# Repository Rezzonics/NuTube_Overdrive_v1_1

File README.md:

# NuTube_Overdrive_v1_1 (EAGLE 6.3.0)
NuTube Overdrive guitar pedal

Eagle CAD 6.3.0:
- Eagle CAD Schematics (.sch)
- Eagle CAD Layout (.brd)
- Bill of Materials (txt, csv, xlsx)
- Components library (.lbr)

FreeCAD 16.0:
 - 3D CAD NuTube Overdrive enclosure
 
A <a href="https://www.youtube.com/watch?v=pDtBdqI9vC8&list=PLVcOAdxtwYCBdqzgB6T4JSNhljZ__4p3t">guitar pedal test video Youtube playlist<a>

# Disclaimer:
This is just an amateur pedal with no intention for profit or to infringe any trademark.
Tube Screamer is a trademark of Hoshino Gakki Co.
This pedal is not for sale. If you want to buy a similar pedal I recommend you <a href="http://www.ibanez.com/products/u_effect_page18.php?year=2018&amp;area_id=&amp;cat_id=6&amp;series_id=153&amp;effect_id=39">Ibanez NTS Screamer<a>

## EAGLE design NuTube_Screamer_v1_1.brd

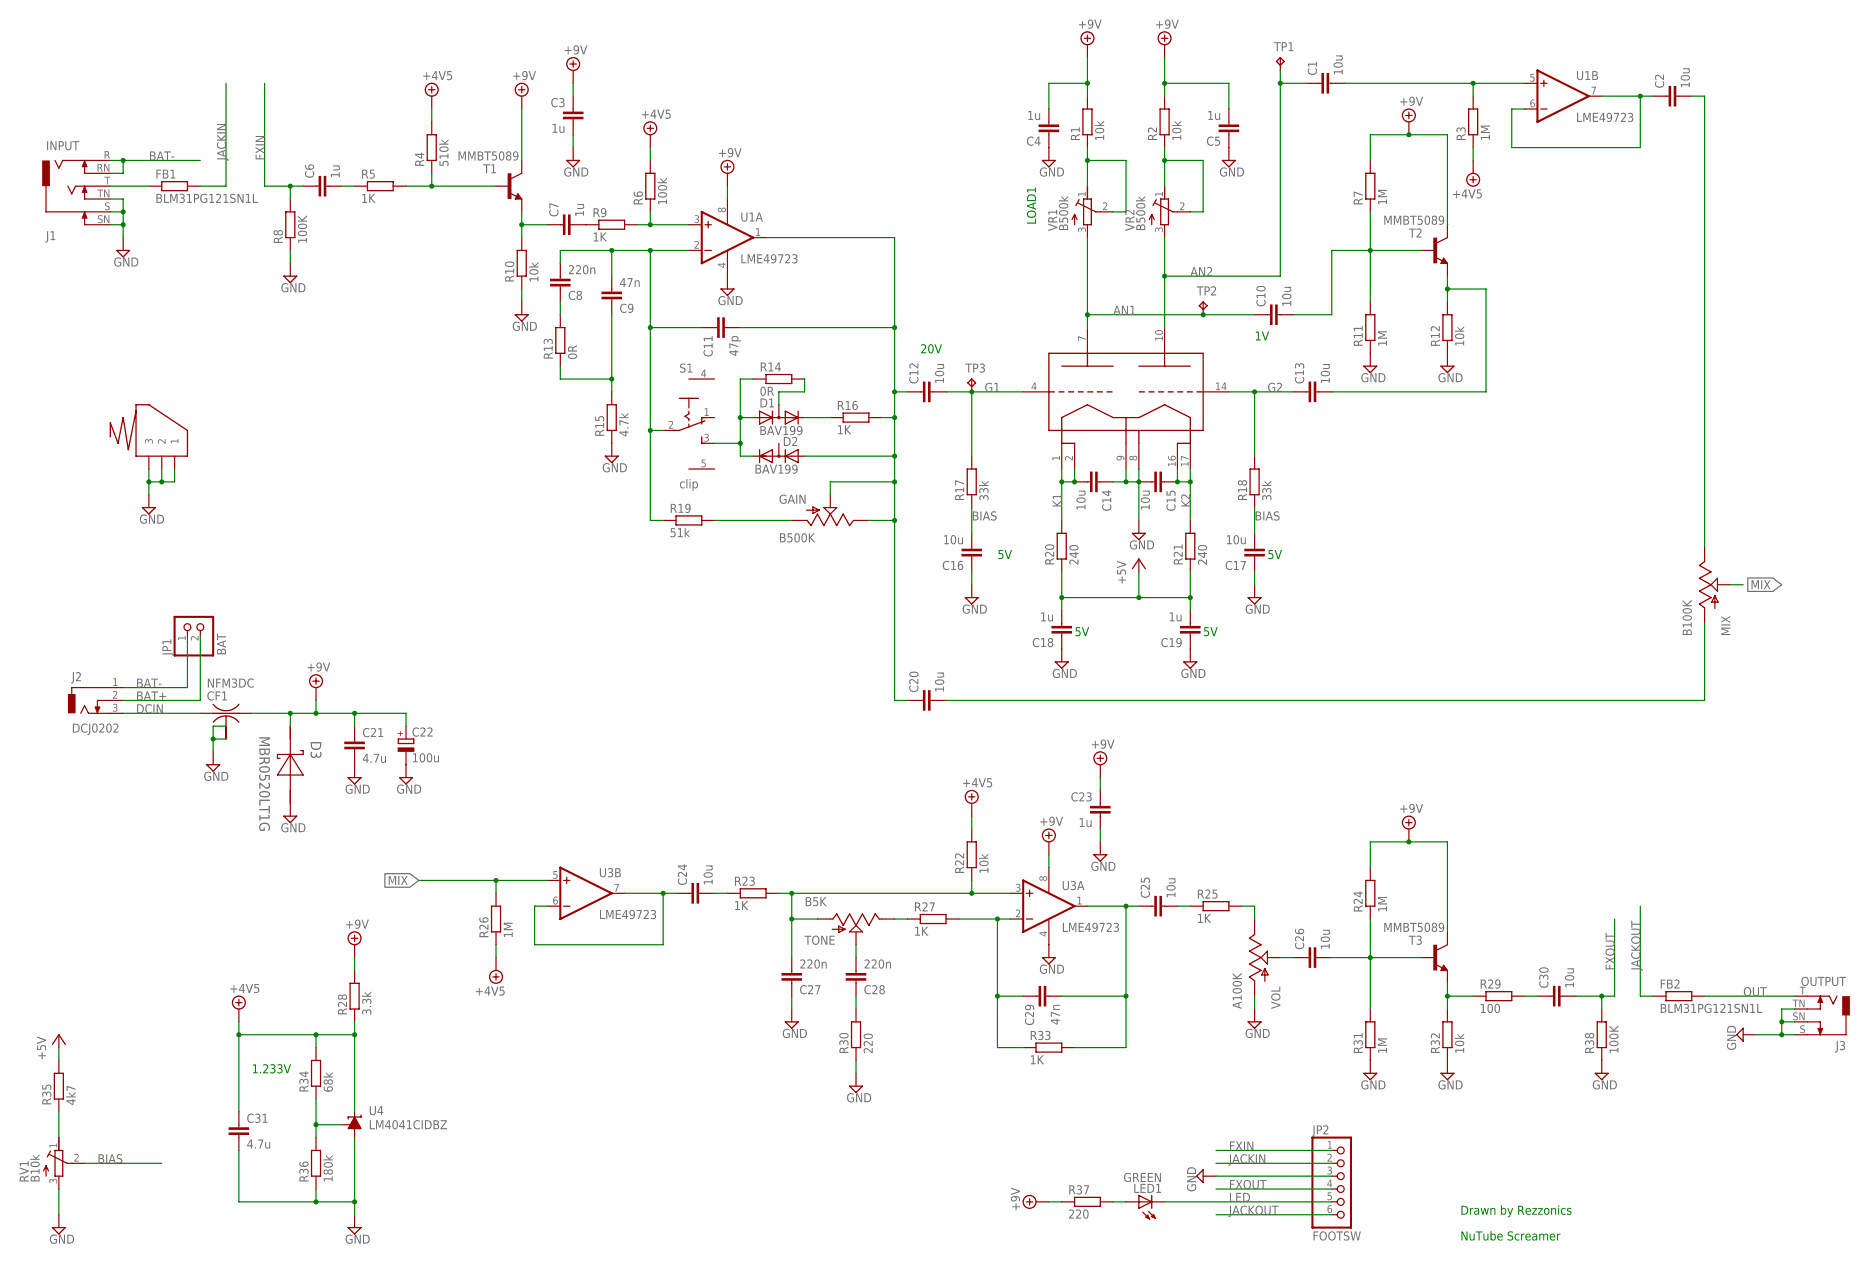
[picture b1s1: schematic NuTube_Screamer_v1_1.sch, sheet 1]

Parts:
C1, C2, C10, C12, C14, C15, C16, C17, C20, C24, C25, C26, C30: 10u; C0805K; MPN GRM21BR6YA106KE43L
C3, C6, C7, C23: 1u; C0603K; MPN GRM188R71H104KA93D
C4, C5, C18, C19: 1u; C0603K; MPN C1608X5R1H105K080AB
C8, C27, C28: 220n; C0603K; MPN GRM188R71H104KA93D
C9, C29: 47n; C0603K; MPN GRM188R71H104KA93D
C11: 47p; C0603K; MPN GRM188R71H104KA93D
C13: 10u; C0805K; PARTNO GRM21BR6YA106KE43L
C21, C31: 4.7u; C0805K; MPN GRM21BR61E475KA12L
C22: 100u; PANASONIC_D; MPN EEE-1VA101XP
CF1: NFM3DC; MPN NFM3DPC223R1H3L
D1, D2: BAV199; SOT23; PARTNO BAV199235
D3: MBR0520LT1G; SOD-123; MPN MBR0520LT1G
FB1, FB2: BLM31PG121SN1L; R1206; MPN BLM31PG121SN1L
GAIN: B500K; ALPS_POT; PARTNO PTV09A-4020S-B504
J1: INPUT; NEUTRIK-NMJ6HCD2; MPN NMJ6HCD2
J2: DCJ0202; MPN 163-179PH-EX
J3: OUTPUT; NEUTRIK-NMJ4HCD2; MPN NMJ4HCD2
JP1: BAT; 1X02; MPN *
JP2: FOOTSW; 1X06; MPN *
LED1: GREEN; LED5MM; MPN SSL-LX5093GD
MIX: B100K; ALPS_POT; PARTNO PTV09A-4020S-B104
R1, R2: 10k; R0603; MPN ERJ-2RKF1002X
R3, R7, R11, R24, R26, R31: 1M; R0603@1; MPN CR0603-FX-1004ELF
R4: 510k; R0603@1; MPN CR0603-FX-1004ELF
R5, R9, R16, R23, R25, R27, R33: 1K; R0603@1; MPN CR0603-FX-1002HLF
R6: 100k; R0603@1; MPN CR0603-FX-1004ELF
R8, R38: 100K; R0603@1; MPN CR0603-FX-1004ELF
R10, R12, R22, R32: 10k; R0603@1; MPN CR0603-FX-1004ELF
R13, R14: 0R; R0603@1; MPN CR0603-FX-1002HLF
R15: 4.7k; R0603@1; MPN CR0603-FX-1004ELF
R17, R18: 33k; R0603; MPN ERJ-2RKF3302X
R19: 51k; R0603@1; MPN CR0603-FX-1002HLF
R20, R21: 240; R0603; MPN ERJ-3EKF2400V
R28: 3.3k; R0603@1; MPN RC0603FR-073K3L
R29: 100; R0603@1; MPN CR0603-FX-1002HLF
R30: 220; R0603@1; MPN CR0603-FX-1004ELF
R34: 68k; R0603@1; MPN RC0603FR-0768KL
R35: 4k7; R0603; MPN ERJ-2RKF4701X
R36: 180k; R0603@1; MPN RC0603FR-07180KL
R37: 220; R0603@1; MPN ERJ-PA3F2200V
RV1: B10k; RTRIM3314G; MPN 3314G-2-103E
S1: clip; MHS122K; PARTNO MHS122K
T1, T2, T3: MMBT5089; SOT23-BEC; PARTNO MMBT5089
TONE: B5K; ALPS_POT; PARTNO PTV09A-4020F-B502
TP1, TP2, TP3: TPTP10R; TP10R; MPN *
U1, U3: LME49723; SO08; MPN LME49723MA/NOPB
U2: NUTUBE 6P1; NUTUBE_6P1_1; MPN *
U4: LM4041CIDBZ; DBZ_R-PDSO-G3; MPN LM4041CIDBZR
VOL: A100K; ALPS_POT; PARTNO PTV09A-4020S-A104
VR1, VR2: B500k; RTRIM3314G; MPN 3314G-1-504E
X1: CLIPAAA-CLIPAAA_2; CLIPAAA_2; MPN 591

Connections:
+4.5V: C31.1, R3.1, R4.2, R6.2, R22.2, R26.1, R28.1, R34.2, U4.2 (C)
+5V: C18.2, C19.2, R20.1, R21.1, R35.2; also elsewhere on the board
+9V: C3.1, C4.2, C5.2, C21.1, C22.+, C23.1, CF1.3, D3.1 (K), R1.2, R2.2, R7.2, R24.2, R28.2, R37.1, T1.C, T2.C, T3.C, U1.8 (V+), U3.8 (V+); also elsewhere on the board
AN1: C10.1, TP2.TP, U2.7 (A1_7), VR1.3 (A)
AN2: C1.1, TP1.TP, U2.10 (A2_10), VR2.3 (A)
BAT+: J2.2, JP1.2
BAT-: J1.R, J1.RN, J2.1, JP1.1
BIAS: C16.2, C17.2, R17.1, R18.1, RV1.2 (S)
DCIN: CF1.1, J2.3
FXIN: C6.1, JP2.1, R8.2
FXOUT: C30.2, JP2.4, R38.2
G1: C12.2, R17.2, TP3.TP, U2.4 (G1_4)
G2: C13.1, R18.2, U2.14 (G2_14)
GND: C3.2, C4.1, C5.1, C14.1, C15.2, C16.1, C17.1, C18.1, C19.1, C21.2, C22.-, C23.2, C27.1, C31.2, CF1.2@1 (2), CF1.2@2 (2), D3.2 (A), J1.S, J1.SN, J1.TN, J3.S, J3.SN, J3.TN, JP2.3, R8.1, R10.1, R11.1, R12.1, R15.1, R30.1, R31.1, R32.1, R36.1, R38.1, RV1.3 (A), U1.4 (V-), U2.8 (GND_8), U2.9 (F2_9), U3.4 (V-), U4.3 (A), VOL.P$1 (A), X1.1, X1.2, X1.3; also elsewhere on the board
JACKIN: FB1.2, JP2.2
JACKOUT: FB2.1, JP2.6
K1: C14.2, R20.2, U2.1 (F1_1), U2.2 (F1_2)
K2: C15.1, R21.2, U2.16 (F3_16), U2.17 (F3_17)
LED: JP2.5, LED1.K (C)
MIX: MIX.P$2 (S), R26.2, U3.5 (+IN)
unnamed: C10.2, R7.1, R11.2, T2.B
unnamed: C6.2, R5.1
unnamed: C13.2, R12.2, T2.E
unnamed: FB1.1, J1.T
unnamed: C7.1, R10.2, T1.E
unnamed: R4.1, R5.2, T1.B
unnamed: C7.2, R9.1
unnamed: R6.1, R9.2, U1.3 (+IN)
unnamed: D1.2 (C), R16.1
unnamed: D1.1 (A), D2.2 (C), R14.1, S1.3 (S)
unnamed: D1.3 (AC), R14.2
unnamed: C11.2, C12.1, C20.1, D2.1 (A), GAIN.P$2 (S), GAIN.P$3 (E), R16.2, U1.1 (OUT)
unnamed: C8.2, C9.2, C11.1, R19.1, S1.2, U1.2 (-IN)
unnamed: GAIN.P$1 (A), R19.2
unnamed: R34.1, R36.2, U4.1 (FB)
unnamed: LED1.A, R37.2
unnamed: C8.1, R13.2
unnamed: R35.1, RV1.1 (E)
unnamed: C9.1, R13.1, R15.2
unnamed: C1.2, R3.2, U1.5 (+IN)
unnamed: C2.1, U1.6 (-IN), U1.7 (OUT)
unnamed: C20.2, MIX.P$1 (A)
unnamed: C2.2, MIX.P$3 (E)
unnamed: C27.2, R22.1, R23.2, TONE.P$1 (A), U3.3 (+IN)
unnamed: C24.1, U3.6 (-IN), U3.7 (OUT)
unnamed: C24.2, R23.1
unnamed: C25.1, C29.2, R33.2, U3.1 (OUT)
unnamed: R27.1, TONE.P$3 (E)
unnamed: C28.2, TONE.P$2 (S)
unnamed: C28.1, R30.2
unnamed: C29.1, R27.2, R33.1, U3.2 (-IN)
unnamed: C25.2, R25.1
unnamed: R25.2, VOL.P$3 (E)
unnamed: C26.1, VOL.P$2 (S)
unnamed: C26.2, R24.1, R31.2, T3.B
unnamed: R29.1, R32.2, T3.E
unnamed: C30.1, R29.2
OUT: FB2.2, J3.T
RL1: R1.1, VR1.1 (E), VR1.2 (S)
RL2: R2.1, VR2.1 (E), VR2.2 (S)

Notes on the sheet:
Drawn by Rezzonics
NuTube Screamer
20V
LOAD1
1.233V

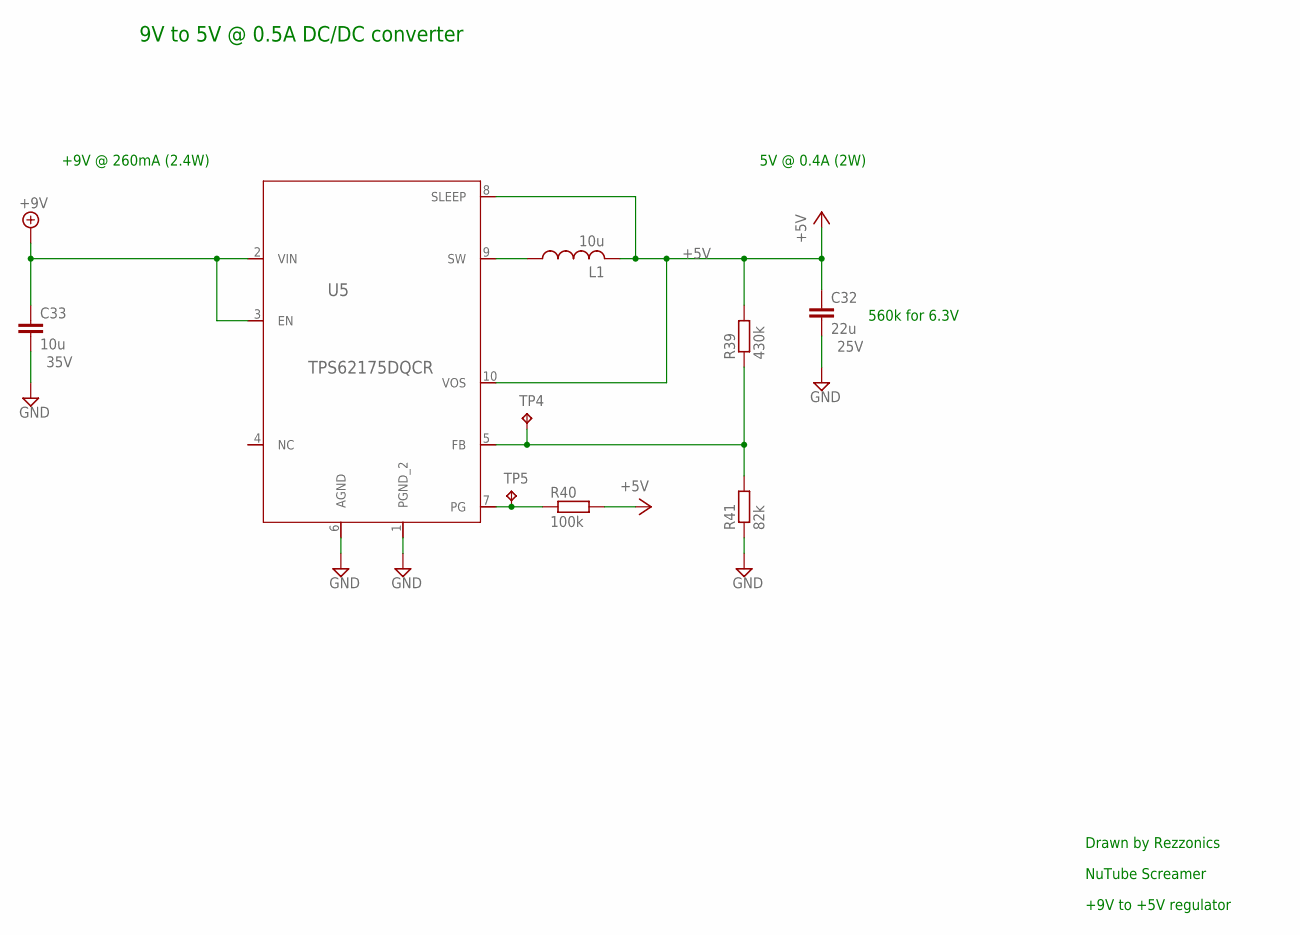
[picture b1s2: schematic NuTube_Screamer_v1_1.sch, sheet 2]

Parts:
C32: 22u; C0805K; MPN C2012X5R1V226M125AC
C33: 10u; C0805K; MPN GRM21BR6YA106KE43L
L1: 10u; SRN4018; MPN SRN4018-100M
R39: 430k; R0603; MPN ERJ-2GEJ434X
R40: 100k; R0603; MPN ERJ-2RKF1003X
R41: 82k; R0603; MPN ERJ-2RKF8202X
TP4, TP5: TPTP10R; TP10R; MPN *
U5: TPS62175DQCR; R-PWSON-N10; MPN TPS62175DQCR

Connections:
+5V: C32.1, L1.2, R39.2, R40.2, U5.8 (SLEEP), U5.10 (VOS); also elsewhere on the board
+9V: C33.1, U5.2 (VIN), U5.3 (EN); also elsewhere on the board
GND: C32.2, C33.2, R41.1, U5.1 (PGND_2), U5.6 (AGND); also elsewhere on the board
unnamed: R40.1, TP5.TP, U5.7 (PG)
unnamed: L1.1, U5.9 (SW)
VCC3: R39.1, R41.2, TP4.TP, U5.5 (FB)

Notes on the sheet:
+9V @ 260mA (2.4W)
9V to 5V @ 0.5A DC/DC converter
5V @ 0.4A (2W)
560k for 6.3V
Drawn by Rezzonics
NuTube Screamer
+9V to +5V regulator

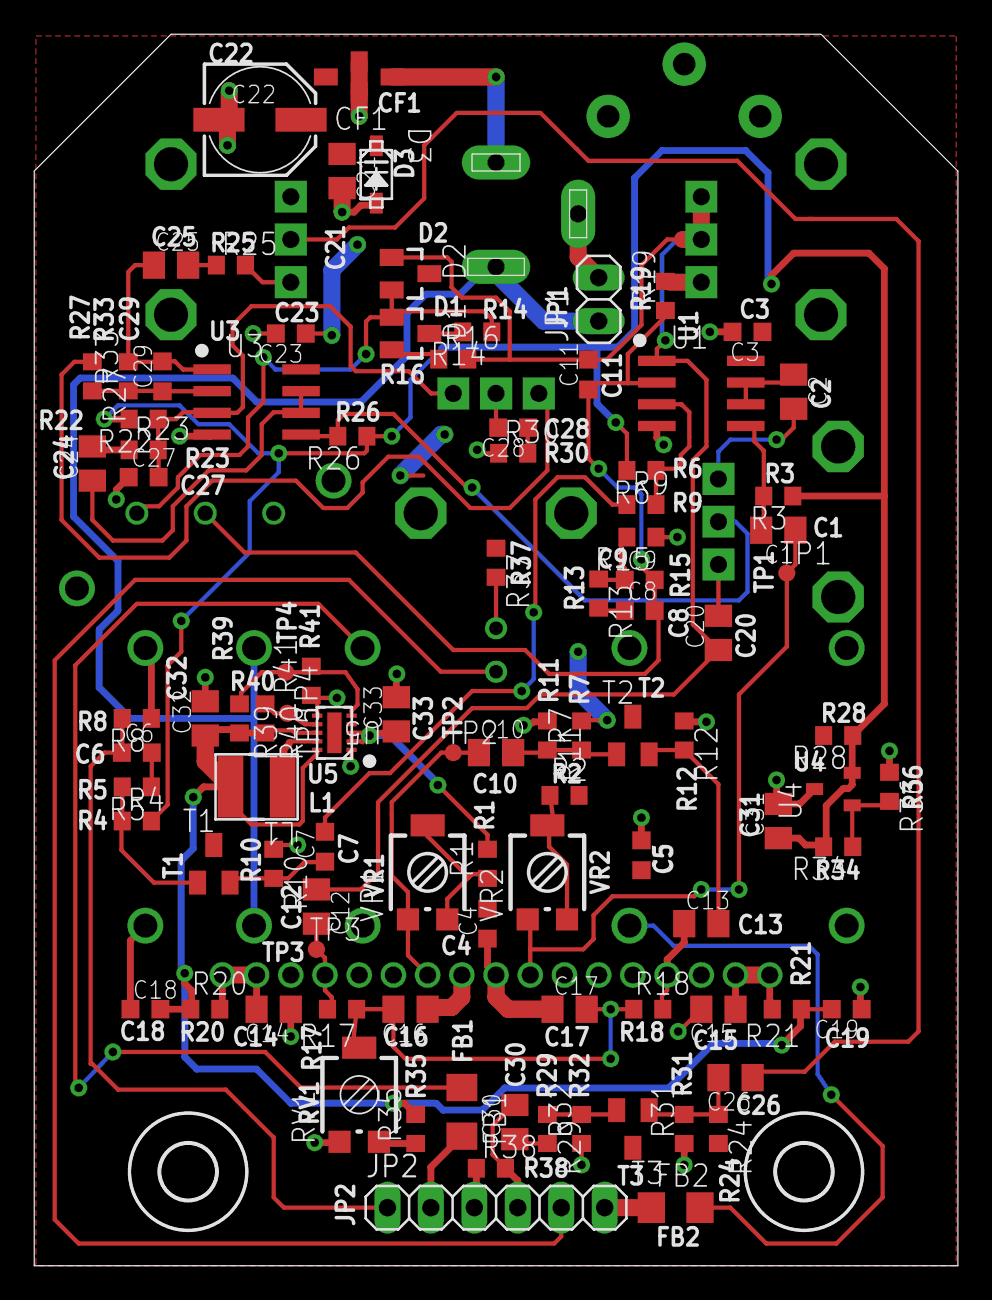
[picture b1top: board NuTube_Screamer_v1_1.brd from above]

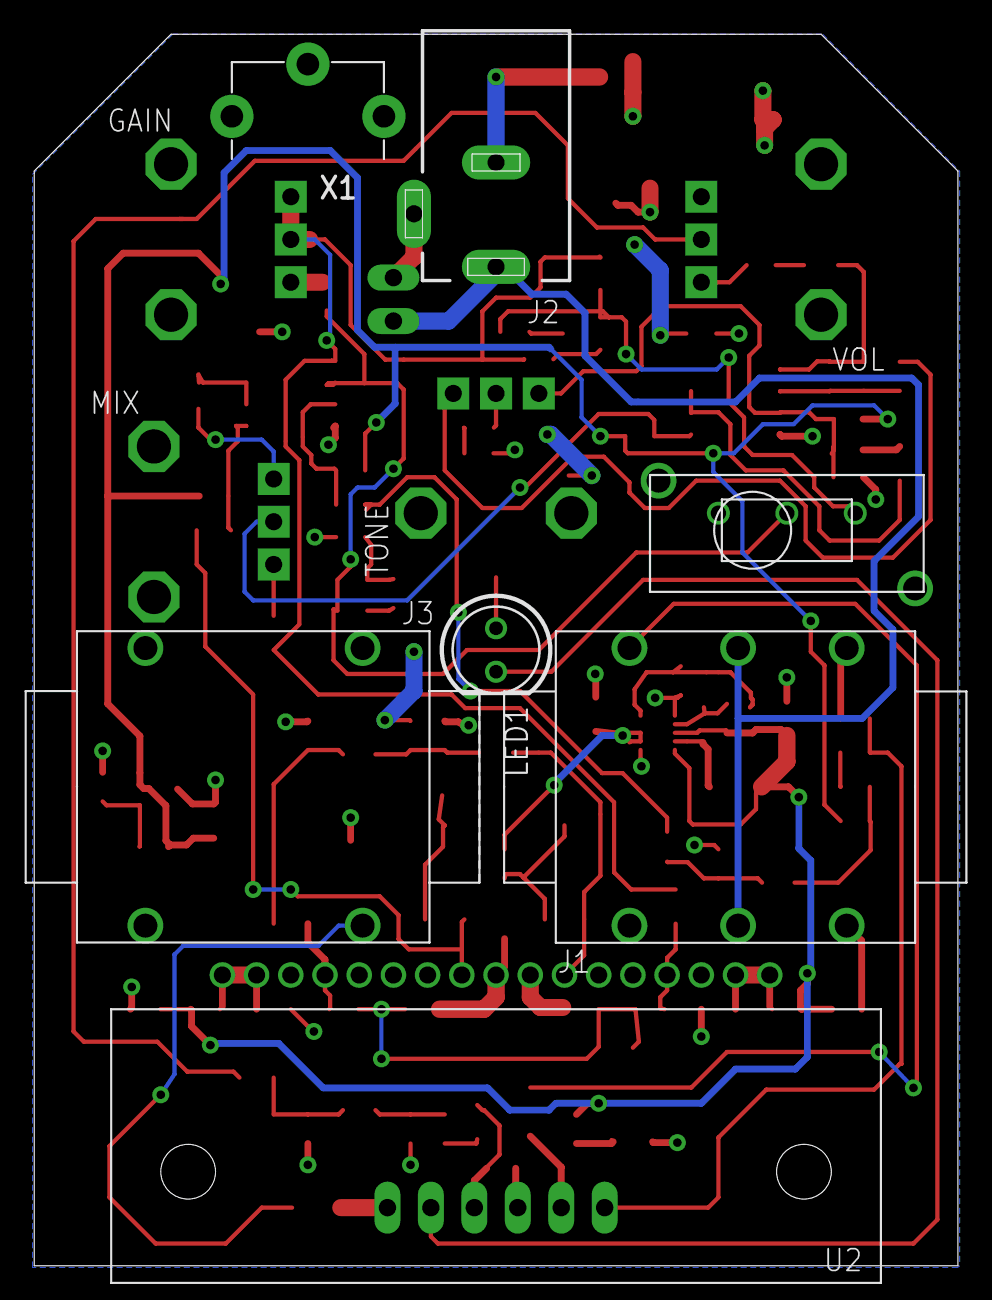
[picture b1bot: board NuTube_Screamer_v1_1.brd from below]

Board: 2 copper layers, 54.0 x 72.0 mm, 111 parts (11 on the bottom side), 63 nets.

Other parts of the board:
U$1, U$2: 3,2

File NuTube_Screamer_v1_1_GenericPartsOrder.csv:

Part Number,Mfg Name,VID,Vendor Part Num,Description,Customer Ref,Part Value,Tol,Size,Qty-1,Qty-5,Qty-25,Part References,Value,XX
CRCW06030000ZSTB,Vishay,ME,71-CRCW0603000ZT-RT5,Thick Film Resistors - SMD 0603 1/10watt ZEROohm Jumper,res013,0,*,*,2,10,50,"R13, R14",0R,X
ERJ-3EKF1001V,Panasonic,ME,667-ERJ-3EKF1001V,Thick Film Resistors - SMD 0603 1Kohms 1% Tol,res018,1k,*,*,7,35,175,"R5, R9, R16, R23, R25, R27, R33",1K,X
CR0603-FX-1004ELF,Bourns,ME,652-CR0603FX-1004ELF,Thick Film Resistors - SMD 0603 1M 1% 1/10W,res003,1M,*,*,7,35,175,"R3, R7, R8, R11, R24, R26, R31",1M,X
C1608X7R1V105K080AE,TDK,ME,810-C1608X7R1V105KAE,CAP CER 1UF 35V 10% X7R 0603,capcer067,1u,10%,*,8,40,200,"C3, C4, C5, C6, C7, C18, C19, C23",1u,X
RC0603FR-073K3L,Yageo,ME,603-RC0603FR-073K3L,Thick Film Resistors - SMD 0603 3.3kohms 1% Tol,res139,3.3k,*,*,1,5,25,R28,3.3k,X
ERJ-3EKF4701V,Panasonic,ME,667-ERJ-3EKF4701V,Thick Film Resistors - SMD 0603 4.7Kohms 1% Tol,res027,4.7k,*,*,1,5,25,R15,4.7k,X
C2012X5R1E475K125AB,TDK,ME,810-C2012X5R1E475K,CAP CER 4.7uF 25volts X5R 10% 0805,capcer006,4.7u,10%,*,2,10,50,"C21, C31",4.7u,X
ERJ-3EKF4701V,Panasonic,ME,667-ERJ-3EKF4701V,Thick Film Resistors - SMD 0603 4.7Kohms 1% Tol,res027,4.7k,*,*,1,5,25,R35,4k7,X
CR0603-FX-1002HLF,Bourns,ME,652-CR0603-FX1002HLF,Thick Film Resistors - SMD 0603 10KOHM 1/10WATT 1%,res002,10k,*,*,6,30,150,"R1, R2, R10, R12, R22, R32",10k,X
GRM21BR6YA106KE43L,Murata,ME,81-GRM21BR6YA106KE3L,CAP CER 10UF 35V X5R 0805,capcer075,10u,*,805,15,75,375,"C1, C2, C10, C12, C13, C14, C15, C16, C17, C20, C24, C25, C26, C30, C33",10u,X
SRN4018-100M,Bourns,ME,652-SRN4018-100M,FIXED IND 10UH 1.3A 180 MOHM SMD,ind010,10u,*,*,1,5,25,L1,10u,X
C2012X5R1V226M125AC,TDK,ME,810-C2012X5R1V226MAC,CAP CER 22UF 35V X5R 0805,capcer078,22u,*,*,1,5,25,C32,22u,X
CR0603-FX-3302ELF,Bourns,ME,652-CR0603FX-3302ELF,Thick Film Resistors - SMD 0603 33K ohm 1%,res008,33k,*,*,2,10,50,"R17, R18",33k,X
06035D473MAT2A,AVX,ME,581-06035D473MAT2A,CAP CER 0.047UF 50V X5R 0603,capcer086,47n,20%,603,2,10,50,"C9, C29",47n,X
GCM1885C2A470JA16D,Murata,ME,81-GCM1885C2A470J16D,CAP CER 47PF 100V C0G/NP0 0603,capcer087,47p,5%,603,1,5,25,C11,47p,X
ERJ-3EKF5102V,Panasonic,ME,667-ERJ-3EKF5102V,Thick Film Resistors - SMD 0603 51Kohms 1% Tol,res046,51k,*,*,1,5,25,R19,51k,X
RC0603FR-0768KL,Yageo,ME,603-RC0603FR-0768KL,Thick Film Resistors - SMD 0603 68kohms 1% Tol,res138,68k,*,*,1,5,25,R34,68k,X
ERJ-3EKF8202V,Panasonic,ME,667-ERJ-3EKF8202V,RES SMD 82K OHM 1% 1/10W 0603,res042,82k,*,*,1,5,25,R41,82k,X
RC0603FR-07100RL,Yageo,ME,603-RC0603FR-07100RL,RES SMD 100 OHM 1% 1/10W 0603,res131,100,*,*,1,5,25,R29,100,X
ERJ-3EKF1003V,Panasonic,ME,667-ERJ-3EKF1003V,RES SMD 100K OHM 1% 1/10W 0603,res048,100k,*,*,2,10,50,"R6, R40",100k,X
EEE-1VA101XP,Panasonic,ME,667-EEE-1VA101XP,CAP ALUM 100UF 20% 35V SMD,capelec002,100u,*,*,1,5,25,C22,100u,X
RC0603FR-07180KL,Yageo,ME,603-RC0603FR-07180KL,Thick Film Resistors - SMD 0603 180K 1% 1/10W,res006,180k,*,*,1,5,25,R36,180k,X
ERJ-PA3F2200V,Panasonic,ME,667-ERJ-PA3F2200V,RES SMD 220 OHM 1% 1/4W 0603,res132,220,*,*,2,10,50,"R30, R37",220,X
GRM188R61H224KAC4D,Murata,ME,81-GRM188R61H224KACD,CAP CER 0.22UF 50V X5R 0603,capcer088,220n,10%,603,3,15,75,"C8, C27, C28",220n,X
ERJ-3EKF2400V,Panasonic,ME,667-ERJ-3EKF2400V,RES SMD 240 OHM 1% 1/10W 0603,res121,240,*,*,2,10,50,"R20, R21",240,X
CR0603-FX-4303ELF,Bourns,ME,652-CR0603FX-4303ELF,Thick Film Resistors - SMD 0603 430K ohm 1%,res010,430k,*,*,1,5,25,R39,430k,X
CR0603-FX-5103ELF,Bourns,ME,652-CR0603FX-5103ELF,Thick Film Resistors - SMD 0603 510kohms 1% Tol,res140,510k,1%,603,1,5,25,R4,510k,X
PTV09A-4020S-A104,Bourns,ME,652-PTV09A4020SA104,Potentiometers 9mm 100Kohms Audio,pot024,A100K,*,*,1,5,25,VOL,A100K,X
PTV09A-4020F-B502,Bourns,ME,652-PTV09A-4020FB502,Potentiometers 9mm 5Kohms Linear,pot023,B5K,*,*,1,5,25,TONE,B5K,X
3314G-2-103E,Bourns,ME,652-3314G-2-103E,TRIMMER 10K OHM 0.25W SMD,pottrim005,B10k,*,*,1,5,25,RV1,B10k,X
PTV09A-4020S-B104,Bourns,ME,652-PTV09A4020SB104,Potentiometers 9mm 100Kohms Linear,pot025,B100K,*,*,1,5,25,MIX,B100K,X
PTV09A-4020S-B504,Bourns,ME,652-PTV09A4020SB504,Potentiometers 9mm 500Kohms Linear,pot026,B500K,*,*,1,5,25,GAIN,B500K,X
3314G-1-504E,Bourns,ME,652-3314G-1-504E,TRIMMER 500K OHM 0.25W SMD,pottrim003,B500k,*,*,2,10,50,"VR1, VR2",B500k,X
BAV199235,NXP,ME,771-BAV199235,Rectifiers DIODE LOW LEAKAGE,diode002,BAV199,*,*,2,10,50,"D1, D2",BAV199,X
BLM31PG121SN1L,Murata,ME,81-BLM31PG121SN1L,EMI Filter Beads Chips & Arrays 1206 120 OHM,fer002,120,*,*,2,10,50,"FB1, FB2",BLM31PG121SN1L,X
591,Keystone electronics,ME,534-591,Cylindrical Battery Contacts Clips Holders & Springs AA/AAA SPRING CONT,con025,591,*,*,1,5,25,X1,CLIPAAA-CLIPAAA_2,X
PJ-202A,CUI,ME,490-PJ-202A,CONN POWER JACK 2.1MM PCB,con014,PJ-202A,*,*,1,5,25,J2,DCJ0202,X
SSL-LX5093GD,Lumex,ME,696-SSL-LX5093GD,LED GRN DIFF 5MM ROUND T/H,led010,Green,*,*,1,5,25,LED1,GREEN,X
NMJ4HCD2,REAN,ME,550-12202,Phone Connectors 2C MONO 2-SPST NC,con005,*,*,*,1,5,25,J1,INPUT,X
LM4041CIDBZR,Texas Instruments,ME,595-LM4041CIDBZR,Voltage References Adjustable Precision Mcrpwr Shunt .5%,vref002,LM4041CIDBZR,*,*,1,5,25,U4,LM4041CIDBZ,X
LME49723MA/NOPB,Texas Instruments,ME,926-LME49723MA/NOPB,Audio Amplifiers Dual Audio Op Amp,icopamp002,LME49723,*,*,2,10,50,"U1, U3",LME49723,X
MBR0520LT1G,ON Semiconductor,ME,863-MBR0520LT1G,Schottky Diodes & Rectifiers 0.5A 20V,diodes006,MBR0520,*,*,1,5,25,D3,MBR0520LT1G,X
MMBT5089,Fairchild Semiconductor,ME,512-MMBT5089,Transistors Bipolar - BJT NPN Transistor General Purpose ,bjt001,MMBT5089,*,*,3,15,75,"T1, T2, T3",MMBT5089,X
NFM3DPC223R1H3L,Murata,ME,81-NFM3DPC223R1H3L,EMI/RFI Suppressors & Ferrites 0.022uF 50V 2A',fer001,22n,*,*,1,5,25,CF1,NFM3DC,X
831-87-032-10-001101,APEM Inc.,ME,437-8318703210001101,Conn SIP Socket Strip SKT 32 POS 2mm Solder ST Thru-Hole,con024,831-87-032-10-001101,*,*,1,5,25,U2,NUTUBE 6P1,X
NMJ4HCD2,REAN,ME,550-12202,Phone Connectors 2C MONO 2-SPST NC,con005,*,*,*,1,5,25,J3,OUTPUT,X
TPS62175DQCR,Texas Instruments,ME,595-TPS62175DQCR,IC REG BUCK BST ADJ 0.5A 10WSON,icreg009,TPS62175,*,*,1,5,25,U5,TPS62175DQCR,X
1249,Keystone electronics,ME,534-1249,Test Points TP TERM BRS MATTE TINNED PLATED,tp001,*,*,*,5,25,125,"TP1, TP2, TP3, TP4, TP5",TPTP10R,X
MHS122K,APEM Inc.,ME,642-MHS122K,SWITCH SLIDE SPDT 300MA 30V,sw0013,MHS122K,*,*,1,5,25,S1,clip,X

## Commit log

2018-05-13 Create Eagle
